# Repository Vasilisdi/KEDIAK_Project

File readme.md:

# RISKAC Research Program - Environmental Data Collection Project

## Overview

This project, associated with the RISKAC research program, aims to collect environmental data using an electronics system comprising various components. The system is designed to measure temperature, VOC (Volatile Organic Compounds), and other environmental parameters. It utilizes a custom-designed PCB fabricated with KiCAD to provide users with a convenient "plug and play" option. Additionally, the project involves adapting source code for different sensors to meet specific project requirements.

## Tools Used

- SQL
- Python
- Arduino Programming Language
- KiCAD
- Fritzing
- PHP
- 3D Printing

## Components and Features

- **Electronic Components**: The system incorporates a variety of sensors for temperature, VOC, and other environmental data collection.
- **Custom PCB**: Designed with KiCAD, the PCB facilitates easy integration of sensors and ensures efficient communication and power supply.
- **Data Storage and Management**: Data collected by the sensors is stored in CSV files using Spyder platform. The last instance of stored data is then stored in a database for further analysis and retrieval.
- **3D-Printed Case**: A protective case with humidity-removing extruded features has been 3D-printed to safeguard electronic components and ensure reliable operation in varying environmental conditions.

## Project Progression on Kicad

The project began with a power breadboard prototype and evolved into the development of a sophisticated PCB that meets the communication and power supply needs of the integrated sensors. Below is a visual representation of the project in the KiCAD environment:

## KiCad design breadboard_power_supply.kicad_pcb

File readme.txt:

# RISKAC Research Program - Environmental Data Collection Project

## Overview

This project, associated with the RISKAC research program, aims to collect environmental data using an electronics system comprising various components. The system is designed to measure temperature, VOC (Volatile Organic Compounds), and other environmental parameters. It utilizes a custom-designed PCB fabricated with KiCAD to provide users with a convenient "plug and play" option. Additionally, the project involves adapting source code for different sensors to meet specific project requirements.

## Tools Used

- SQL
- Python
- Arduino Programming Language
- KiCAD
- Fritzing
- PHP
- 3D Printing

## Components and Features

- **Electronic Components**: The system incorporates a variety of sensors for temperature, VOC, and other environmental data collection.
- **Custom PCB**: Designed with KiCAD, the PCB facilitates easy integration of sensors and ensures efficient communication and power supply.
- **Data Storage and Management**: Data collected by the sensors is stored in CSV files using Spyder platform. The last instance of stored data is then stored in a database for further analysis and retrieval.
- **3D-Printed Case**: A protective case with humidity-removing extruded features has been 3D-printed to safeguard electronic components and ensure reliable operation in varying environmental conditions.

## Project Progression

The project began with a power breadboard prototype and evolved into the development of a sophisticated PCB that meets the communication and power supply needs of the integrated sensors.

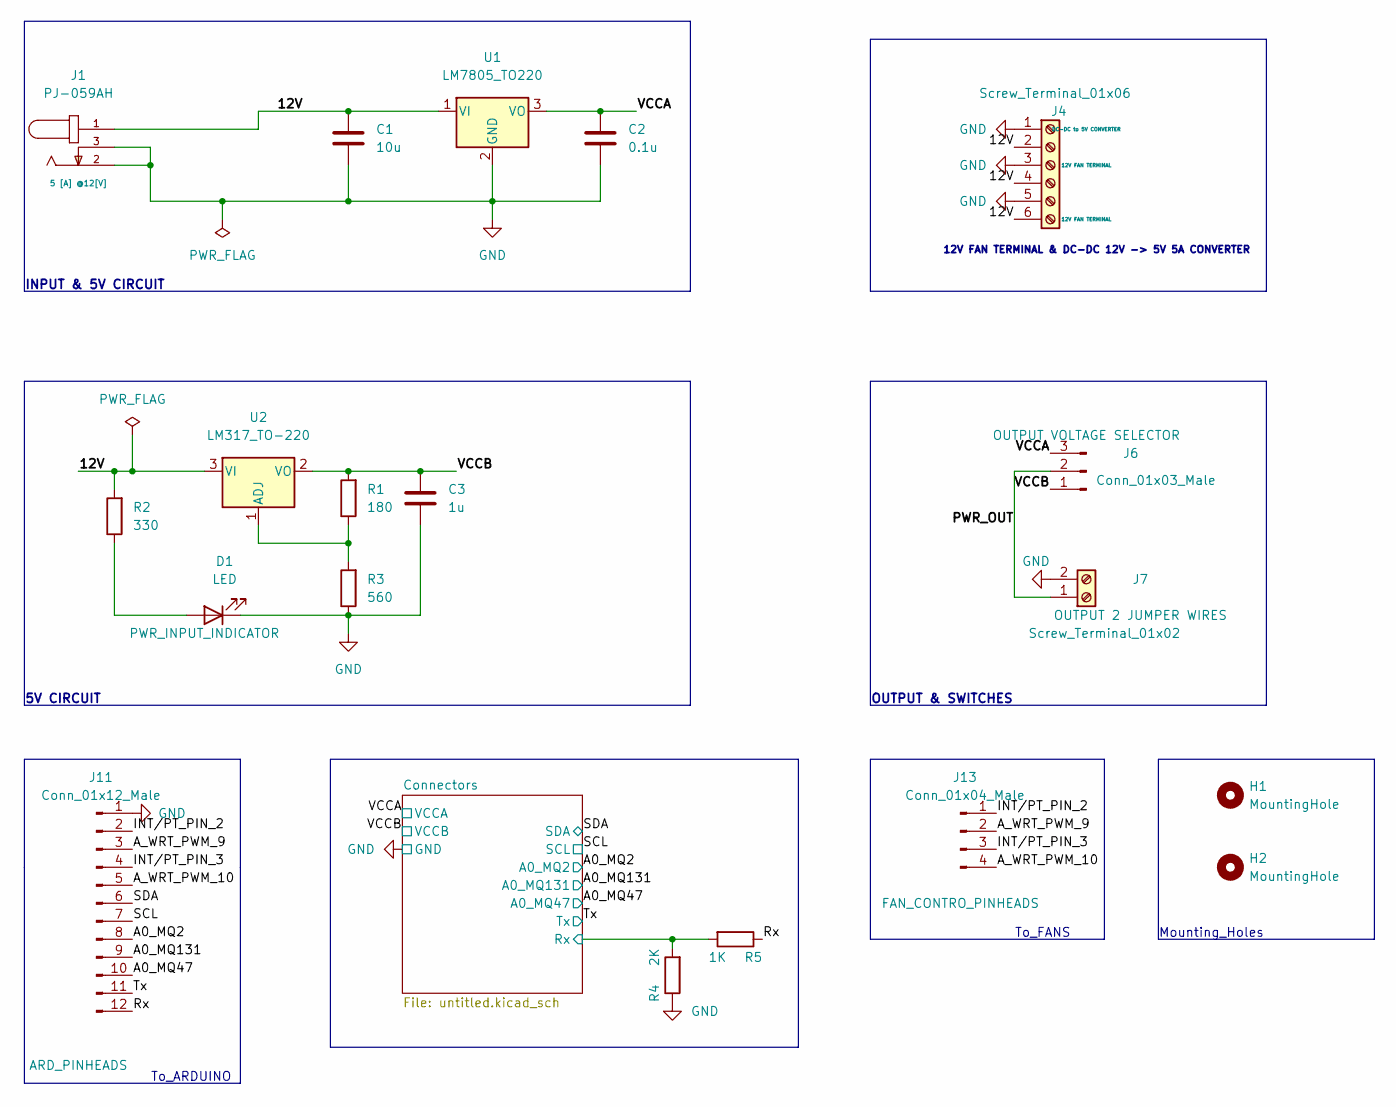
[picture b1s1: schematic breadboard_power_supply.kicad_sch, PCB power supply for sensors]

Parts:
C1: 10u; C_Disc_D3.0mm_W2.0mm_P2.50mm
C2: 0.1u; C_Disc_D3.0mm_W2.0mm_P2.50mm
C3: 1u; C_Disc_D3.0mm_W2.0mm_P2.50mm
D1: LED; LED_D5.0mm
H1, H2: MountingHole; MountingHole_2.7mm
J1: PJ-059AH; CUI_PJ-059AH; Rating 5 [A] @12[V]; PARTREV 1.02
J4: Screw_Terminal_01x06; TerminalBlock_bornier-6_P5.08mm; RATING 8 [A]
J6: Conn_01x03_Male; PinHeader_1x03_P2.54mm_Vertical
J7: Screw_Terminal_01x02; TerminalBlock_bornier-2_P5.08mm; Rating 8 [A]
J11: Conn_01x12_Male; PinSocket_1x12_P2.54mm_Vertical
J13: Conn_01x04_Male; PinSocket_1x04_P2.54mm_Vertical
R1: 180; R_Axial_DIN0204_L3.6mm_D1.6mm_P7.62mm_Horizontal
R2: 330; R_Axial_DIN0204_L3.6mm_D1.6mm_P7.62mm_Horizontal
R3: 560; R_Axial_DIN0204_L3.6mm_D1.6mm_P7.62mm_Horizontal
R4: 2K; R_Axial_DIN0204_L3.6mm_D1.6mm_P7.62mm_Horizontal
R5: 1K; R_Axial_DIN0204_L3.6mm_D1.6mm_P7.62mm_Horizontal
U1: LM7805_TO220; TO-220-3_Vertical; Rating 1 [A]
U2: LM317_TO-220; TO-220-3_Vertical; Rating 1,5 [A]

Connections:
/12V: C1.1, J1.1, J4.2, J4.4, J4.6, R2.2, U1.1 (VI), U2.3 (VI)
/A0_MQ2: J11.8; also elsewhere on the board
/A0_MQ47: J11.10; also elsewhere on the board
/A0_MQ131: J11.9; also elsewhere on the board
/A_WRT_PWM_9: J11.3, J13.2
/A_WRT_PWM_10: J11.5, J13.4
/Connectors/Rx: R4.2, R5.2; also elsewhere on the board
/INT/PT_PIN_2: J11.2, J13.1
/INT/PT_PIN_3: J11.4, J13.3
/PWR_OUT: J6.2, J7.1
/Rx: J11.12, R5.1
/SCL: J11.7; also elsewhere on the board
/SDA: J11.6; also elsewhere on the board
/Tx: J11.11; also elsewhere on the board
/VCCA: C2.1, J6.3, U1.3 (VO); also elsewhere on the board
/VCCB: C3.1, J6.1, R1.2, U2.2 (VO); also elsewhere on the board
GND: C1.2, C2.2, C3.2, D1.1 (K), J1.2, J1.3, J4.1, J4.3, J4.5, J7.2, J11.1, R3.1, R4.1, U1.2 (GND); also elsewhere on the board
unnamed: D1.2 (A), R2.1
unnamed: R1.1, R3.2, U2.1 (ADJ)

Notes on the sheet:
OUTPUT & SWITCHES
5V CIRCUIT
12V FAN TERMINAL & DC-DC 12V -> 5V 5A CONVERTER
INPUT & 5V CIRCUIT
Το_ARDUINO
Το_FANS
Mounting_Holes

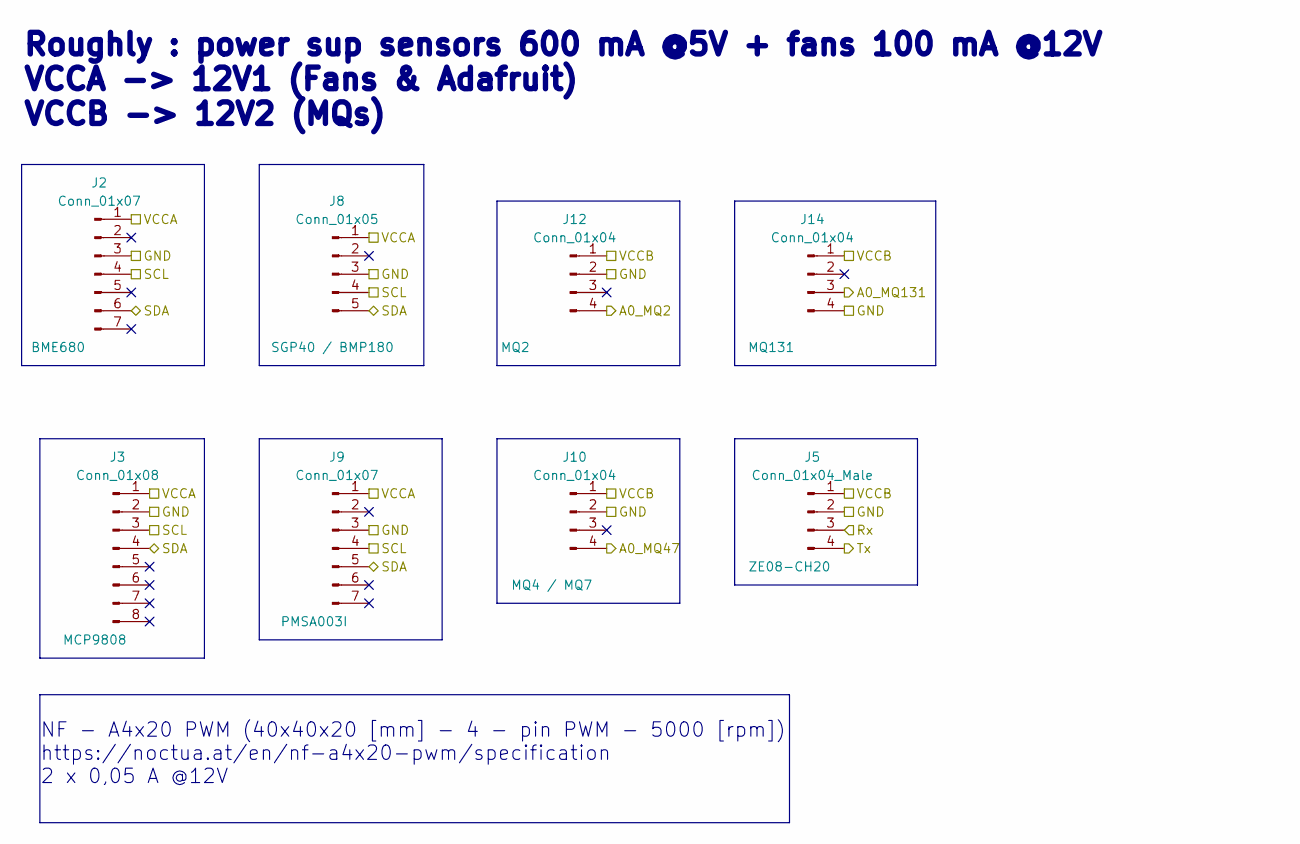
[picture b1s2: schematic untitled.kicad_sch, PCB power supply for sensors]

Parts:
J2, J9: Conn_01x07; PinSocket_1x07_P2.54mm_Vertical
J3: Conn_01x08; PinSocket_1x08_P2.54mm_Vertical
J5: Conn_01x04_Male; PinSocket_1x04_P2.54mm_Vertical
J8: Conn_01x05; PinSocket_1x05_P2.54mm_Vertical
J10, J12, J14: Conn_01x04; PinSocket_1x04_P2.54mm_Vertical

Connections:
/A0_MQ2: J12.4; also elsewhere on the board
/A0_MQ47: J10.4; also elsewhere on the board
/A0_MQ131: J14.3; also elsewhere on the board
/Connectors/Rx: J5.3; also elsewhere on the board
/SCL: J2.4, J3.3, J8.4, J9.4; also elsewhere on the board
/SDA: J2.6, J3.4, J8.5, J9.5; also elsewhere on the board
/Tx: J5.4; also elsewhere on the board
/VCCA: J2.1, J3.1, J8.1, J9.1; also elsewhere on the board
/VCCB: J5.1, J10.1, J12.1, J14.1; also elsewhere on the board
GND: J2.3, J3.2, J5.2, J8.3, J9.3, J10.2, J12.2, J14.4; also elsewhere on the board

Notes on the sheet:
NF - A4x20 PWM (40x40x20 [mm] - 4 - pin PWM - 5000 [rpm]) https://noctua.at/en/nf-a4x20-pwm/specification 2 x 0,05 A @12V
Roughly : power sup sensors 600 mA @5V + fans 100 mA @12V VCCA -> 12V1 (Fans & Adafruit) VCCB -> 12V2 (MQs)

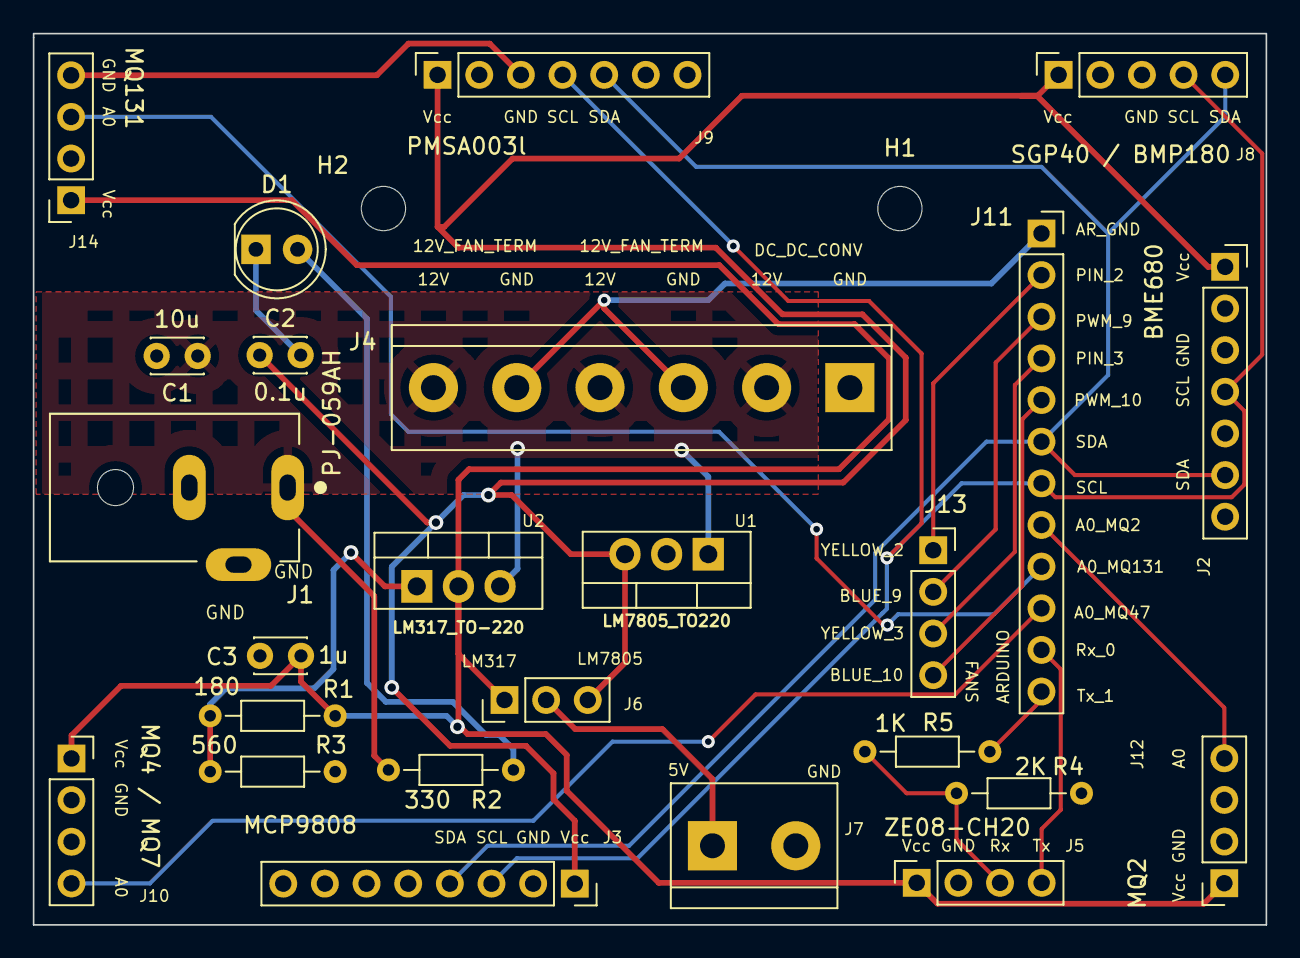
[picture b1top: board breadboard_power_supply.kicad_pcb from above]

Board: 2 copper layers, 75.2 x 54.4 mm, 27 parts (0 on the bottom side), 19 nets.

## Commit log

2022-04-17 Main commission.
2022-04-17 PCB complete design of the power supply.
2022-04-17 Project Target Description
    Target set
2022-05-18 Project Target Description
    Trying to avoid the prl changes also, utilizing gitignore
2022-05-23 Project Target Desctription
2022-05-23 Project Target Description
2022-05-23 Revert "Project Target Description"
    This reverts commit 992a993e3ba41f038e621602d57108eb9190e08b.
2022-05-24 back-up recovery
    I lost the old document, and tried to bring it back extracting a backups file from Supply_and_Sensors branch
2022-05-24 Added some MQs
    needs to be further investigated - to check if it is worth it to install also plain MQ
2022-05-25 Rearrangement
    in order to fit all the new female pin sockets and fit all into a smaller PCB
2022-06-05 Design tweaking
    staging of all the modifications needed , in order to cover the needs of all the power board
2022-06-05 Clear separation of 2 designs : with usb
    consumption calculation , manuals / issue with slider switch to be checked if ok
2022-06-12 Design Rectified
    Added pinheads, all components and parts with their datasheets , power calculations and details - design improvement route tracks thickness check and calculation & F. silkscreening. Remaining : route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
2022-06-12 Design Rectified
    Added pinheads & -sockets, all components and parts with their datasheets , power calculations and details - design improvement route tracks thickness check and calculation & F. silkscreening. Remain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
2022-06-12 Remaining : route tracking
2022-06-13 Routing and Copper - hatch fills
    proceeding
2022-06-14 FINALIZING PCB DESIGN
2022-06-14 MANUFACTURING OF THE PCB
    new path in order to keep all the details in need only
2022-08-03 Redesign of the PCB
2022-08-05 Everything THT before deleting the space marking lines
2022-08-05 BOM & GB FILES
2022-08-07 corrections
2022-08-16 GERBER & PHOTOS INCLUDED
2024-05-16 Project presentation
    This document has been created so as to keep track of the project developments.
2024-05-20 Create LICENSE
